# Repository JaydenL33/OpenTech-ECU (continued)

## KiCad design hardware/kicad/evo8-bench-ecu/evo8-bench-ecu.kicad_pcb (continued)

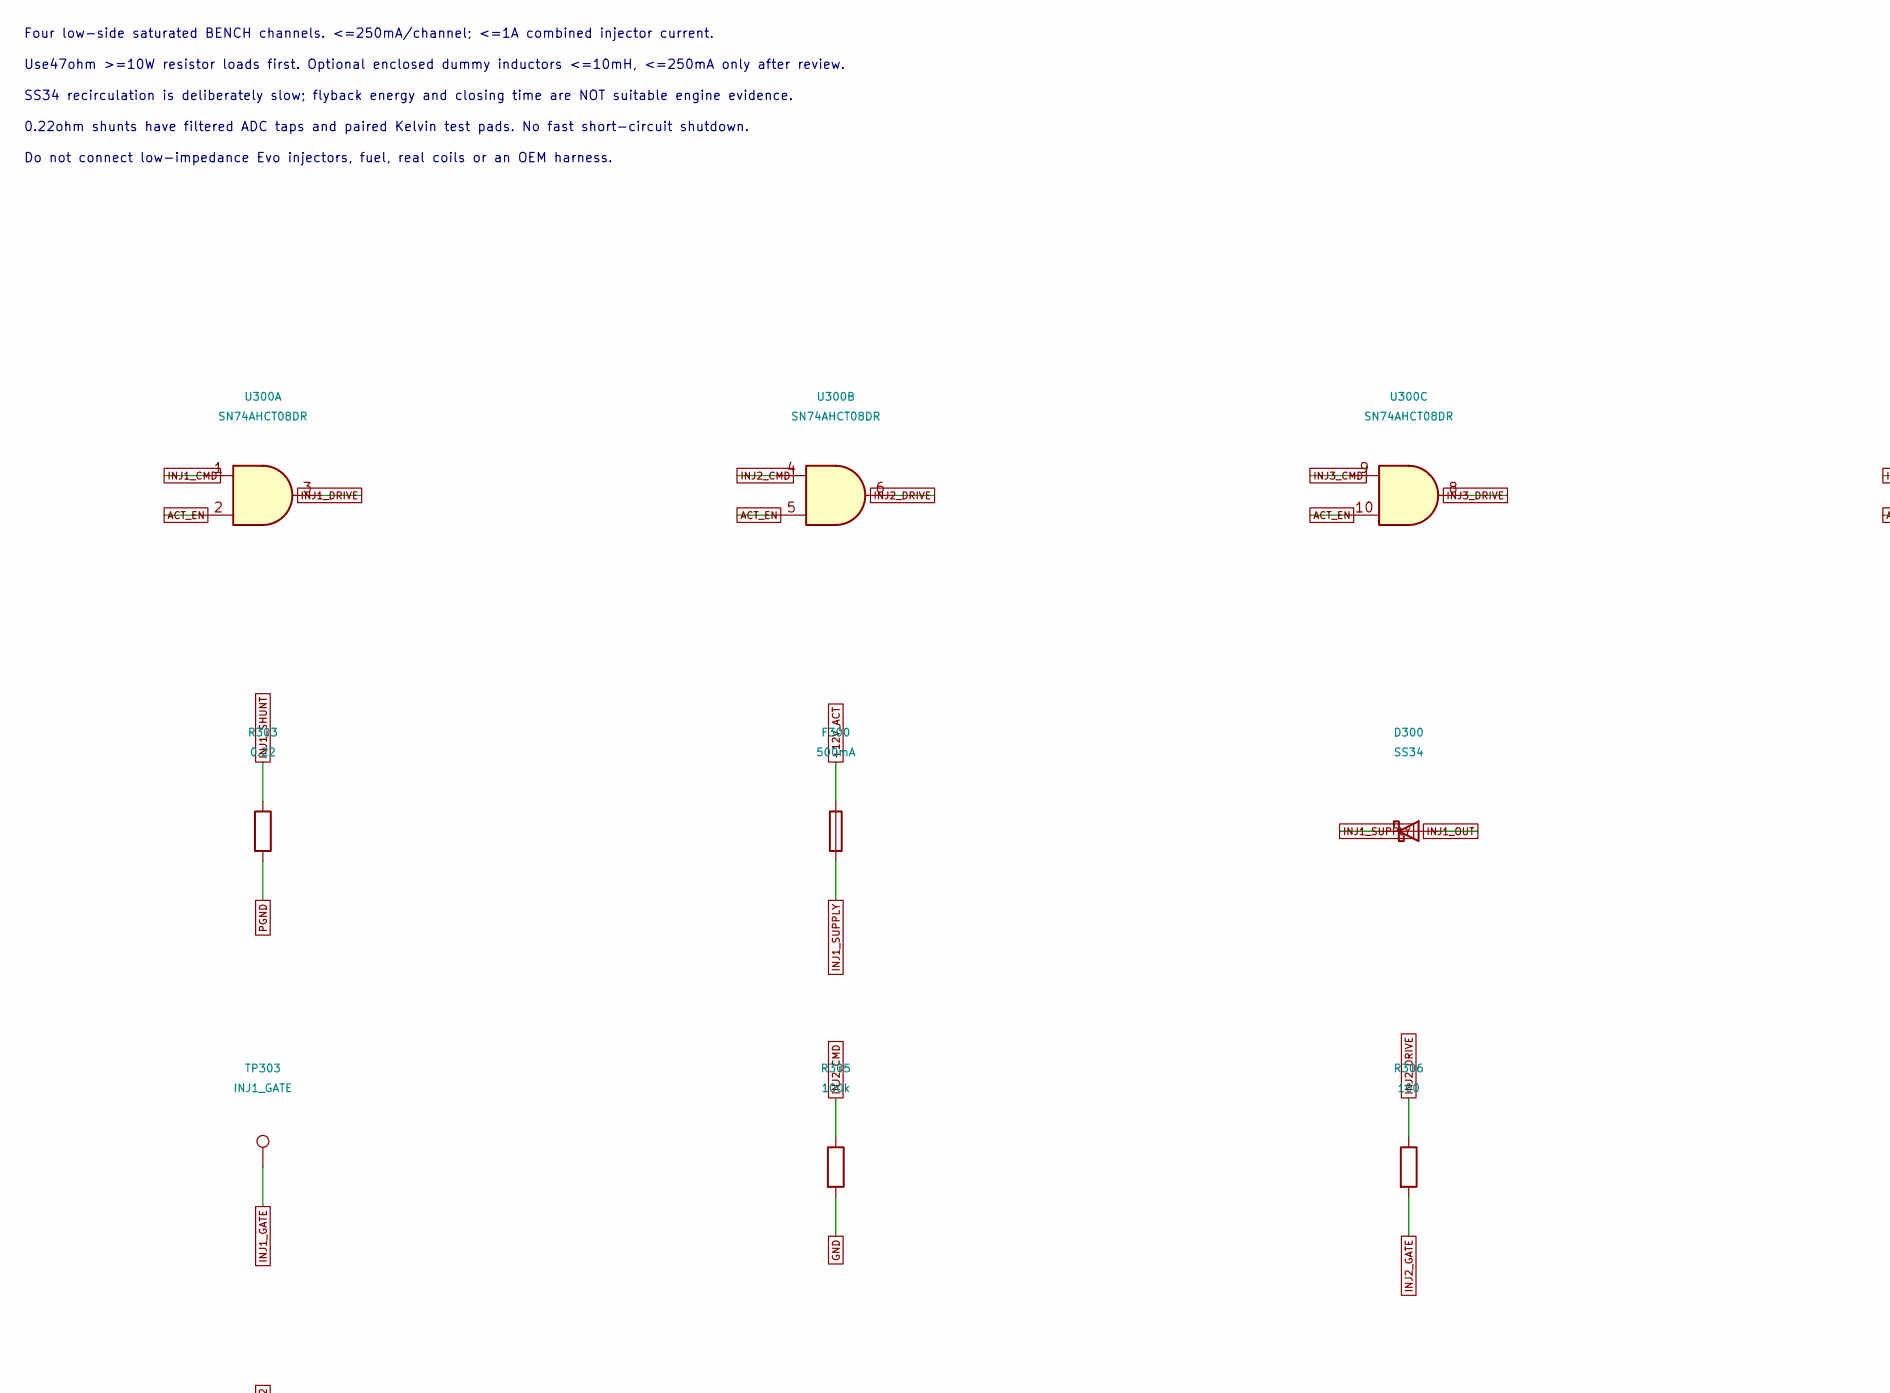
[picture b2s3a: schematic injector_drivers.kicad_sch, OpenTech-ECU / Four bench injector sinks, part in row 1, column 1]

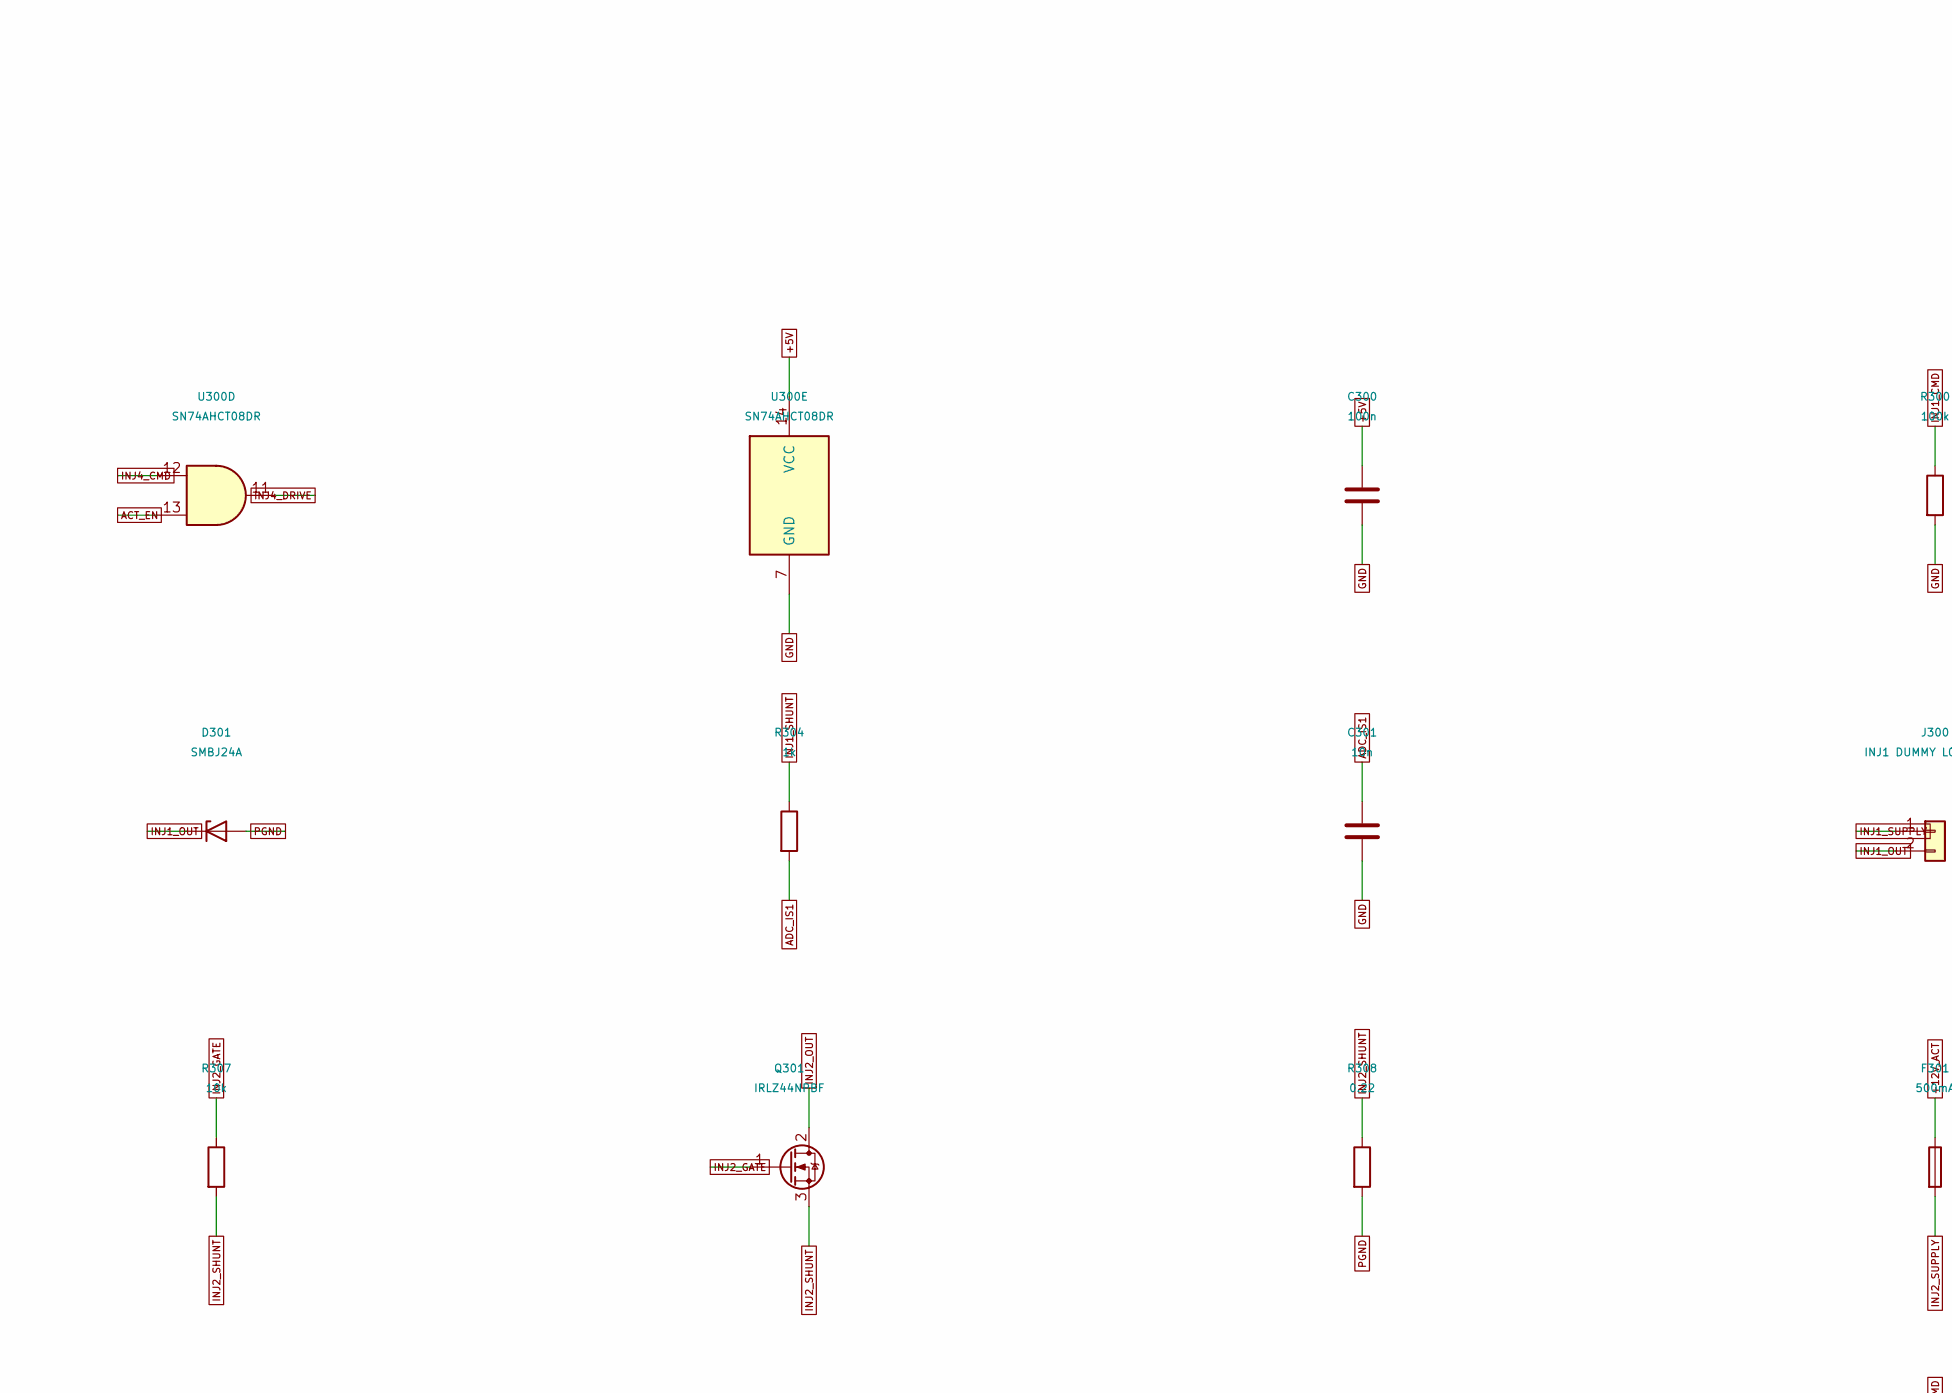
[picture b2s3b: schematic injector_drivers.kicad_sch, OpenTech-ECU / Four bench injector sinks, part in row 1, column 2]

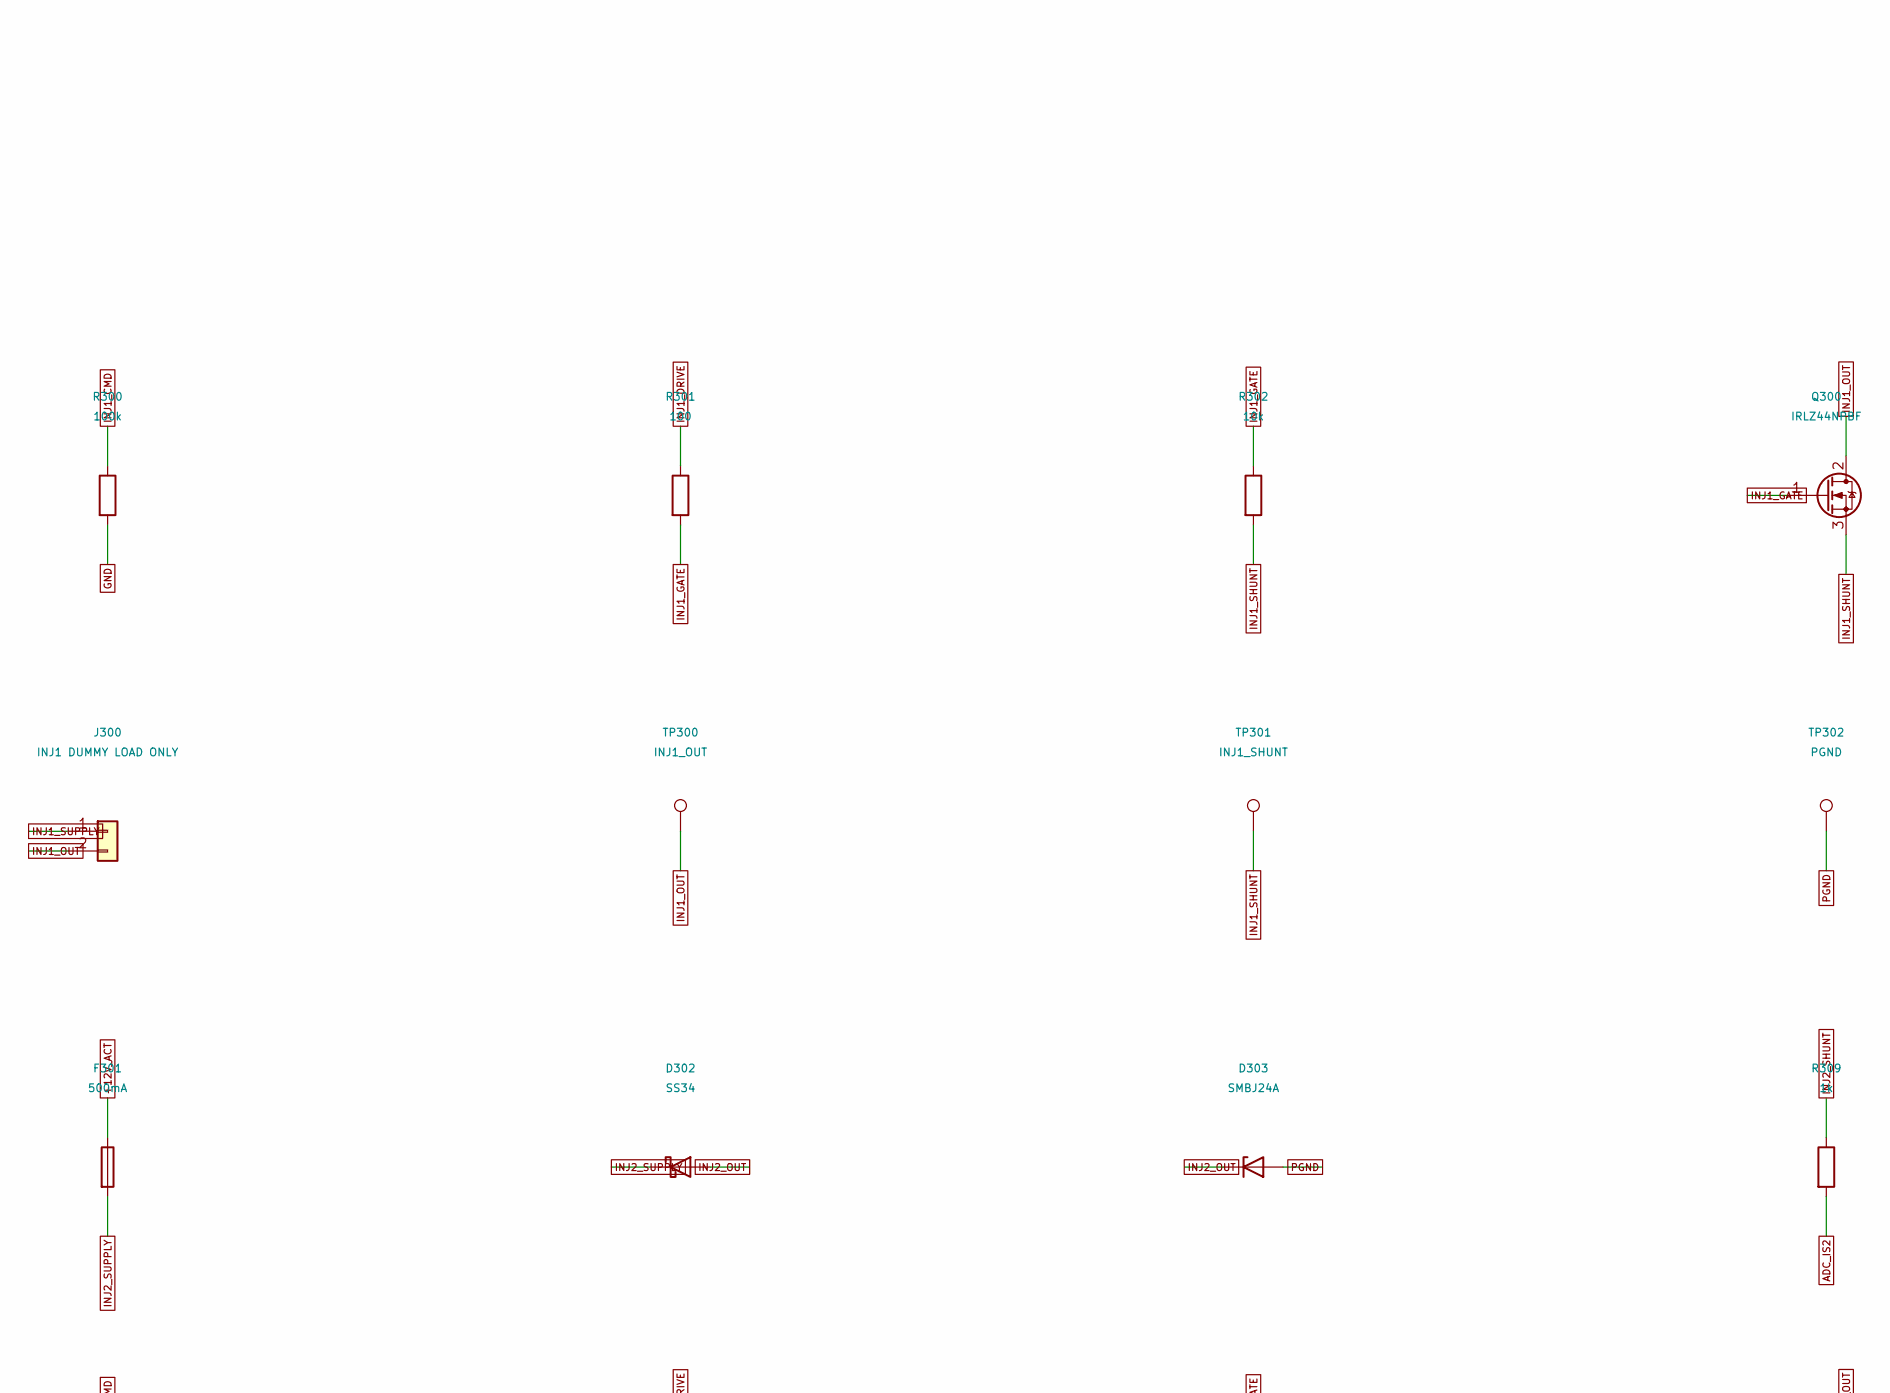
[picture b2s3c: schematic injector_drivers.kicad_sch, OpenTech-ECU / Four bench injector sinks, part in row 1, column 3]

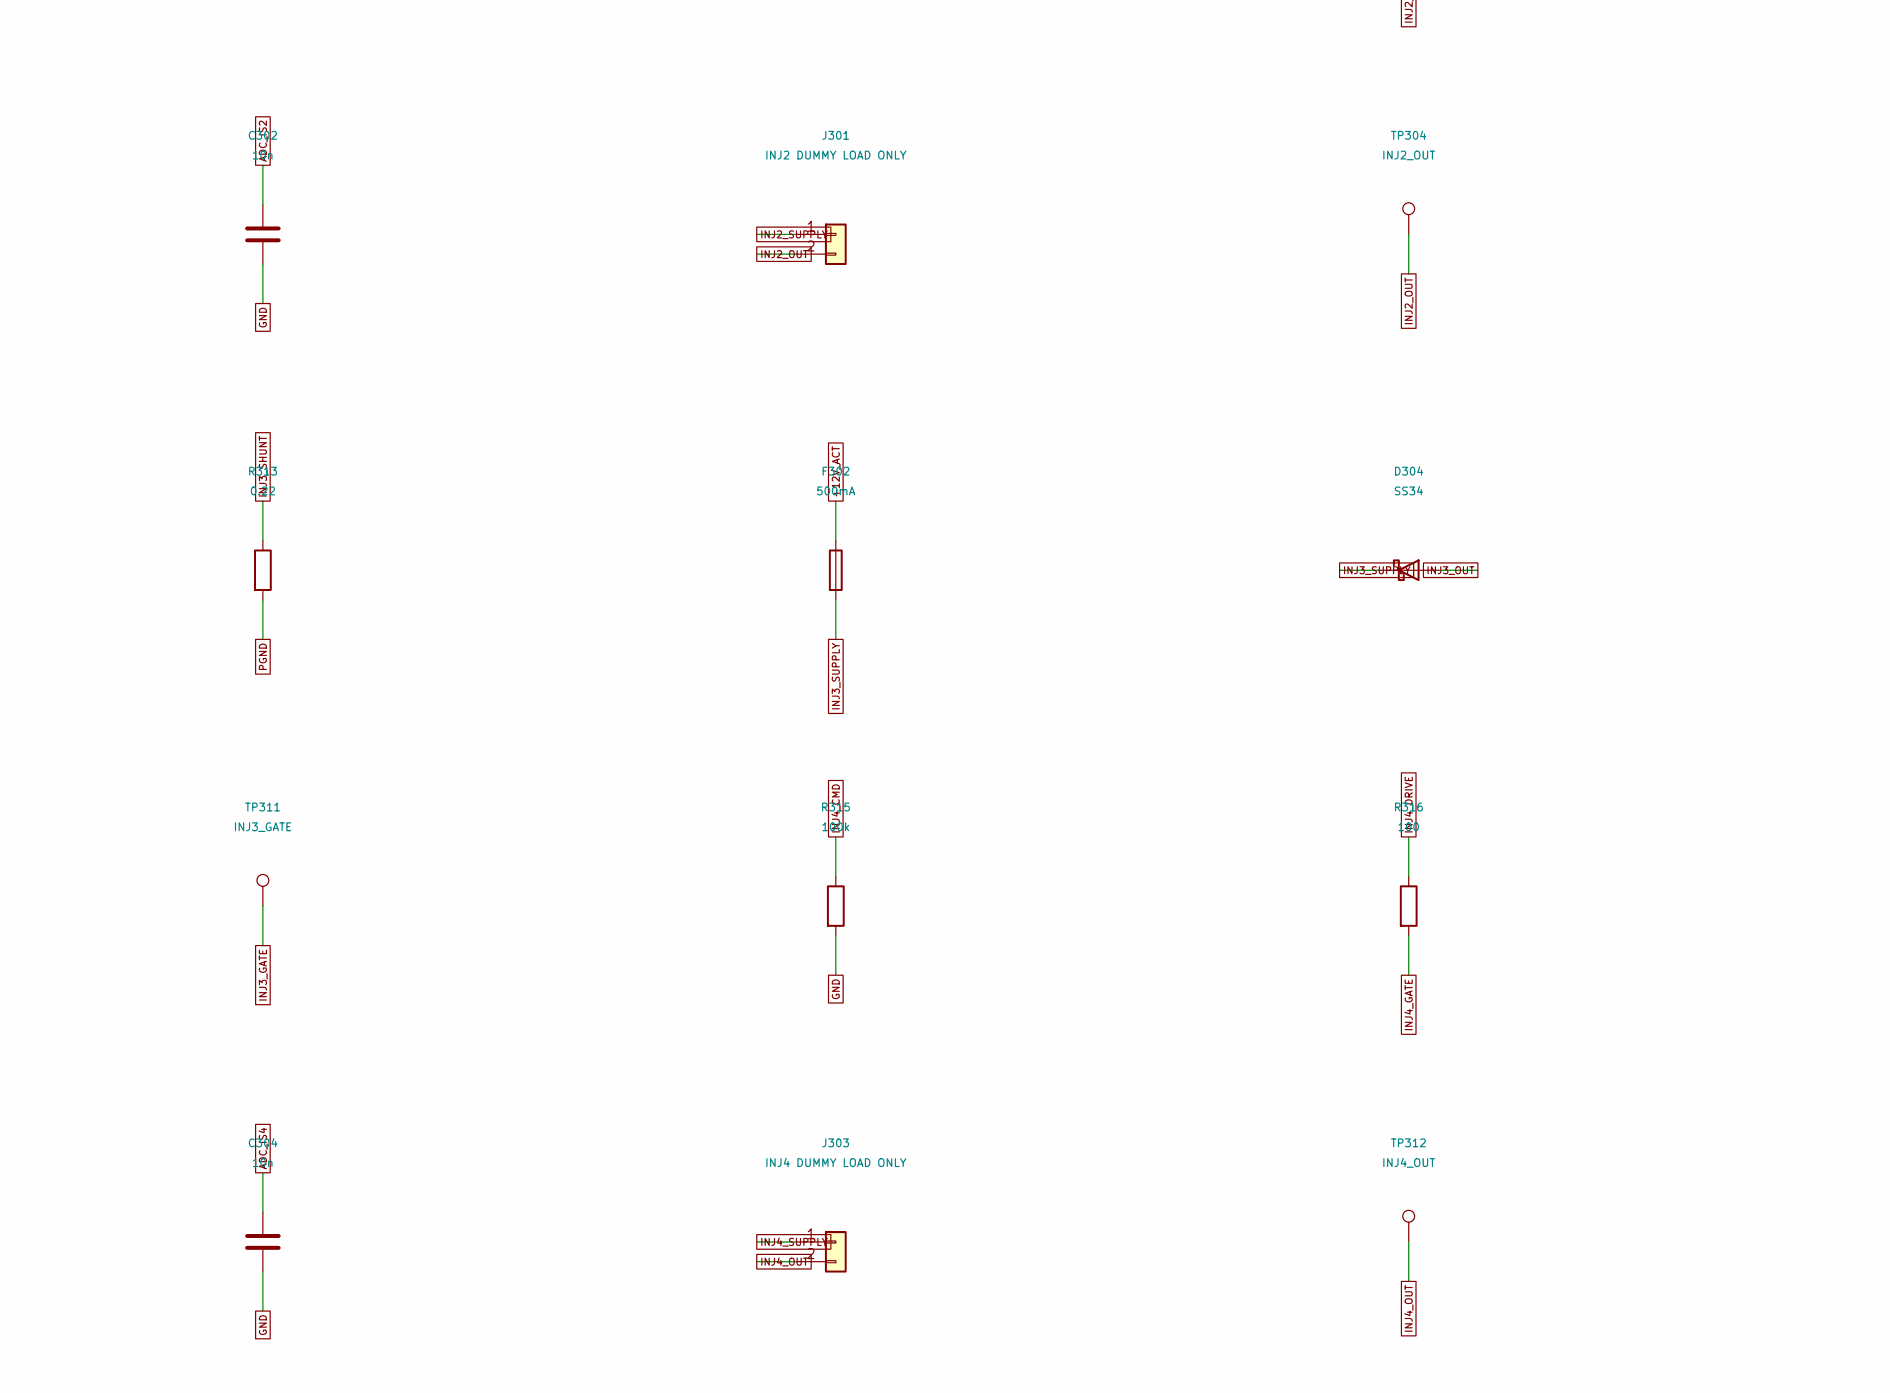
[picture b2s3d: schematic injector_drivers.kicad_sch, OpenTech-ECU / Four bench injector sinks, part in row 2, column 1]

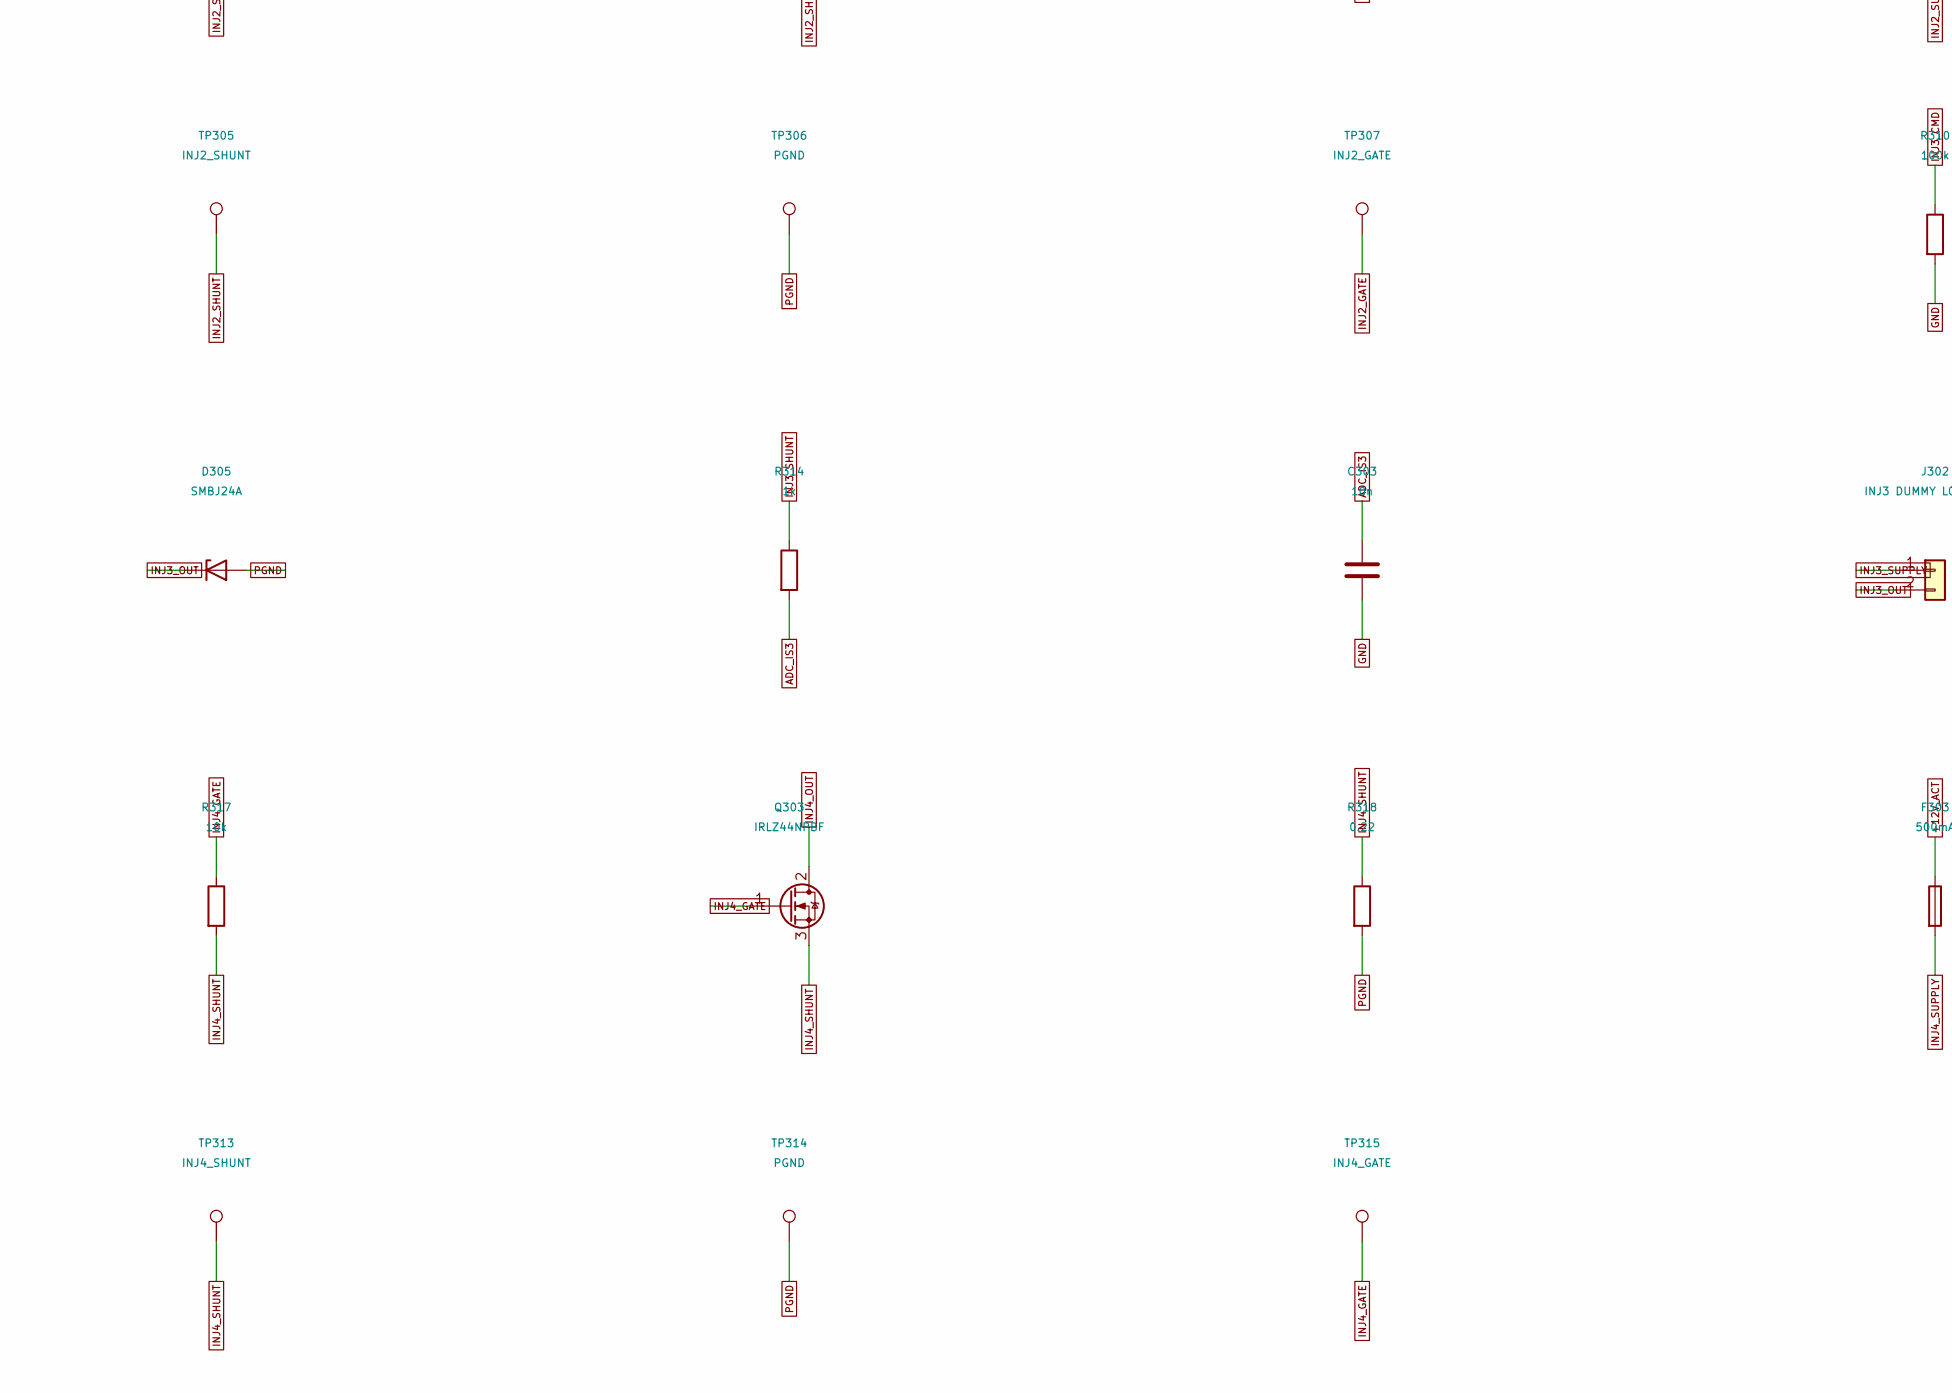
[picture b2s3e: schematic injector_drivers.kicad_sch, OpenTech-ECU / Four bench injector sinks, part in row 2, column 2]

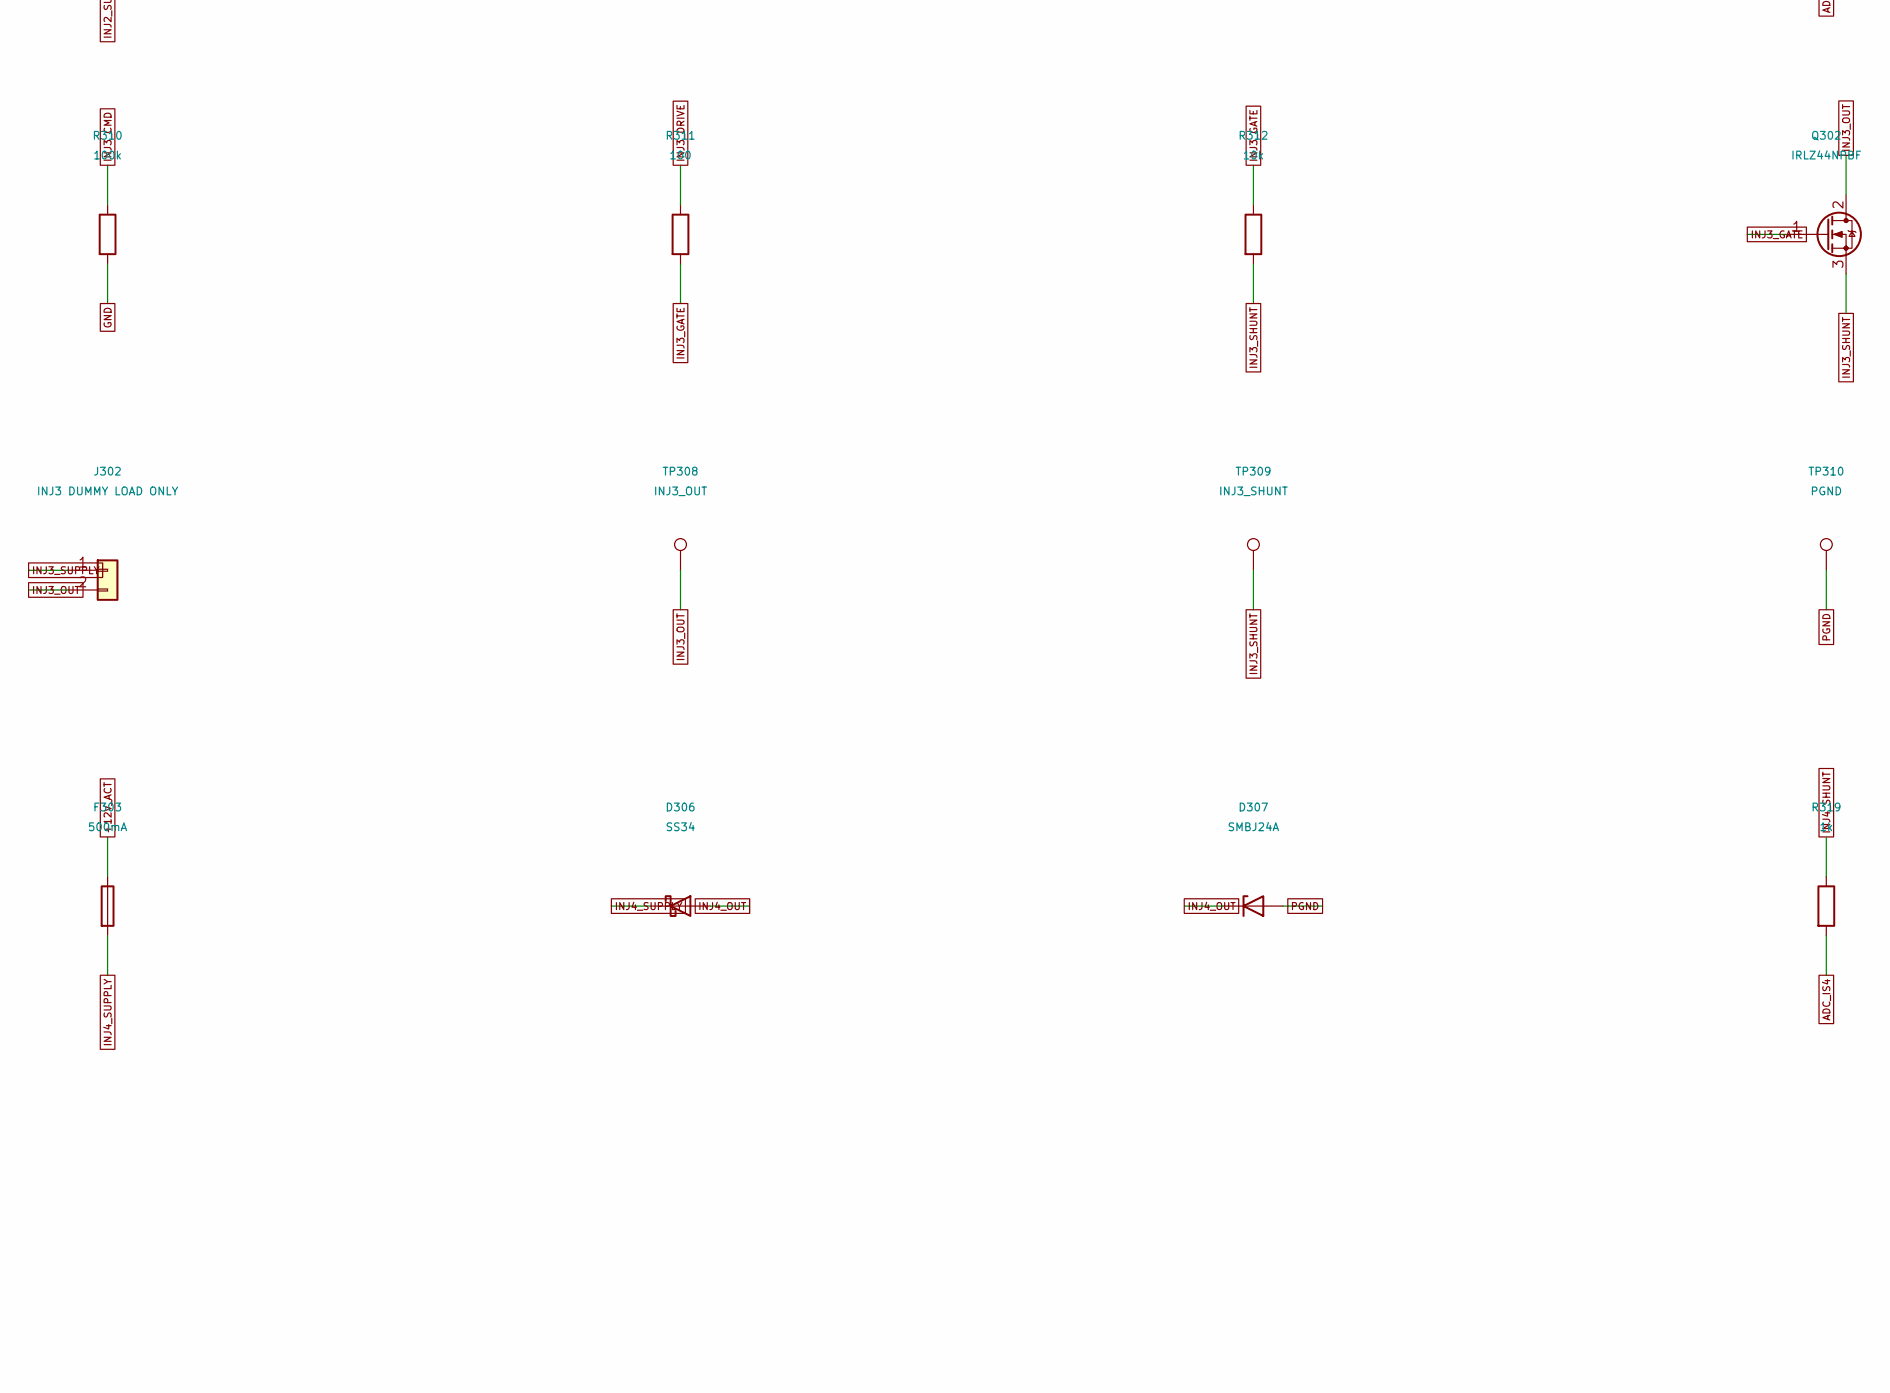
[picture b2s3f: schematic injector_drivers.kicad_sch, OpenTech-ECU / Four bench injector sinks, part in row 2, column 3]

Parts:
C300: 100n; C_0805_2012Metric; MPN GRM21BR71H104KA01L
C301, C302, C303, C304: 10n; C_0805_2012Metric; MPN GRM21BR71H103KA01L
D300, D302, D304, D306: SS34; D_SMA; MPN SS34
D301, D303, D305, D307: SMBJ24A; D_SMB; MPN SMBJ24A
F300, F301, F302, F303: 500mA; Fuse_1206_3216Metric; MPN 0467.500NR
J300: INJ1 DUMMY LOAD ONLY; TerminalBlock_Phoenix_MKDS-1,5-2-5.08_1x02_P5.08mm_Horizont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; MPN 1715721
J301: INJ2 DUMMY LOAD ONLY; TerminalBlock_Phoenix_MKDS-1,5-2-5.08_1x02_P5.08mm_Horizont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; MPN 1715721
J302: INJ3 DUMMY LOAD ONLY; TerminalBlock_Phoenix_MKDS-1,5-2-5.08_1x02_P5.08mm_Horizont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; MPN 1715721
J303: INJ4 DUMMY LOAD ONLY; TerminalBlock_Phoenix_MKDS-1,5-2-5.08_1x02_P5.08mm_Horizont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; MPN 1715721
Q300, Q301, Q302, Q303: IRLZ44NPBF; TO-220-3_Vertical; MPN IRLZ44NPBF
R300, R305, R310, R315: 100k; R_0805_2012Metric; MPN RC0805FR-07100KL
R301, R306, R311, R316: 100; R_0805_2012Metric; MPN RC0805FR-07100RL
R302, R307, R312, R317: 10k; R_0805_2012Metric; MPN RC0805FR-0710KL
R303, R308, R313, R318: 0.22; R_2512_6332Metric; MPN WSL2512R2200FEA
R304, R309, R314, R319: 1k; R_0805_2012Metric; MPN RC0805FR-071KL
TP300: INJ1_OUT; TestPoint_THTPad_D2.0mm_Drill1.0mm; MPN 5010
TP301: INJ1_SHUNT; TestPoint_THTPad_D2.0mm_Drill1.0mm; MPN 5010
TP302, TP306, TP310, TP314: PGND; TestPoint_THTPad_D2.0mm_Drill1.0mm; MPN 5010
TP303: INJ1_GATE; TestPoint_THTPad_D2.0mm_Drill1.0mm; MPN 5010
TP304: INJ2_OUT; TestPoint_THTPad_D2.0mm_Drill1.0mm; MPN 5010
TP305: INJ2_SHUNT; TestPoint_THTPad_D2.0mm_Drill1.0mm; MPN 5010
TP307: INJ2_GATE; TestPoint_THTPad_D2.0mm_Drill1.0mm; MPN 5010
TP308: INJ3_OUT; TestPoint_THTPad_D2.0mm_Drill1.0mm; MPN 5010
TP309: INJ3_SHUNT; TestPoint_THTPad_D2.0mm_Drill1.0mm; MPN 5010
TP311: INJ3_GATE; TestPoint_THTPad_D2.0mm_Drill1.0mm; MPN 5010
TP312: INJ4_OUT; TestPoint_THTPad_D2.0mm_Drill1.0mm; MPN 5010
TP313: INJ4_SHUNT; TestPoint_THTPad_D2.0mm_Drill1.0mm; MPN 5010
TP315: INJ4_GATE; TestPoint_THTPad_D2.0mm_Drill1.0mm; MPN 5010
U300: SN74AHCT08DR; SOIC-14_3.9x8.7mm_P1.27mm; MPN SN74AHCT08DR

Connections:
+5V: C300.1, U300.14 (VCC); also elsewhere on the board
+12V_ACT: F300.1, F301.1, F302.1, F303.1; also elsewhere on the board
ACT_EN: U300.2, U300.5, U300.10, U300.13; also elsewhere on the board
ADC_IS1: C301.1, R304.2; also elsewhere on the board
ADC_IS2: C302.1, R309.2; also elsewhere on the board
ADC_IS3: C303.1, R314.2; also elsewhere on the board
ADC_IS4: C304.1, R319.2; also elsewhere on the board
GND: C300.2, C301.2, C302.2, C303.2, C304.2, R300.2, R305.2, R310.2, R315.2, U300.7 (GND); also elsewhere on the board
INJ1_CMD: R300.1, U300.1; also elsewhere on the board
INJ1_DRIVE: R301.1, U300.3
INJ1_GATE: Q300.1 (G), R301.2, R302.1, TP303.1
INJ1_OUT: D300.2 (A), D301.1 (K), J300.2, Q300.2 (D), TP300.1
INJ1_SHUNT: Q300.3 (S), R302.2, R303.1, R304.1, TP301.1
INJ1_SUPPLY: D300.1 (K), F300.2, J300.1
INJ2_CMD: R305.1, U300.4; also elsewhere on the board
INJ2_DRIVE: R306.1, U300.6
INJ2_GATE: Q301.1 (G), R306.2, R307.1, TP307.1
INJ2_OUT: D302.2 (A), D303.1 (K), J301.2, Q301.2 (D), TP304.1
INJ2_SHUNT: Q301.3 (S), R307.2, R308.1, R309.1, TP305.1
INJ2_SUPPLY: D302.1 (K), F301.2, J301.1
INJ3_CMD: R310.1, U300.9; also elsewhere on the board
INJ3_DRIVE: R311.1, U300.8
INJ3_GATE: Q302.1 (G), R311.2, R312.1, TP311.1
INJ3_OUT: D304.2 (A), D305.1 (K), J302.2, Q302.2 (D), TP308.1
INJ3_SHUNT: Q302.3 (S), R312.2, R313.1, R314.1, TP309.1
INJ3_SUPPLY: D304.1 (K), F302.2, J302.1
INJ4_CMD: R315.1, U300.12; also elsewhere on the board
INJ4_DRIVE: R316.1, U300.11
INJ4_GATE: Q303.1 (G), R316.2, R317.1, TP315.1
INJ4_OUT: D306.2 (A), D307.1 (K), J303.2, Q303.2 (D), TP312.1
INJ4_SHUNT: Q303.3 (S), R317.2, R318.1, R319.1, TP313.1
INJ4_SUPPLY: D306.1 (K), F303.2, J303.1
PGND: D301.2 (A), D303.2 (A), D305.2 (A), D307.2 (A), R303.2, R308.2, R313.2, R318.2, TP302.1, TP306.1, TP310.1, TP314.1; also elsewhere on the board

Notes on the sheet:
Four low-side saturated BENCH channels. <=250mA/channel; <=1A combined injector current.
Use47ohm >=10W resistor loads first. Optional enclosed dummy inductors <=10mH, <=250mA only after review.
SS34 recirculation is deliberately slow; flyback energy and closing time are NOT suitable engine evidence.
0.22ohm shunts have filtered ADC taps and paired Kelvin test pads. No fast short-circuit shutdown.
Do not connect low-impedance Evo injectors, fuel, real coils or an OEM harness.
